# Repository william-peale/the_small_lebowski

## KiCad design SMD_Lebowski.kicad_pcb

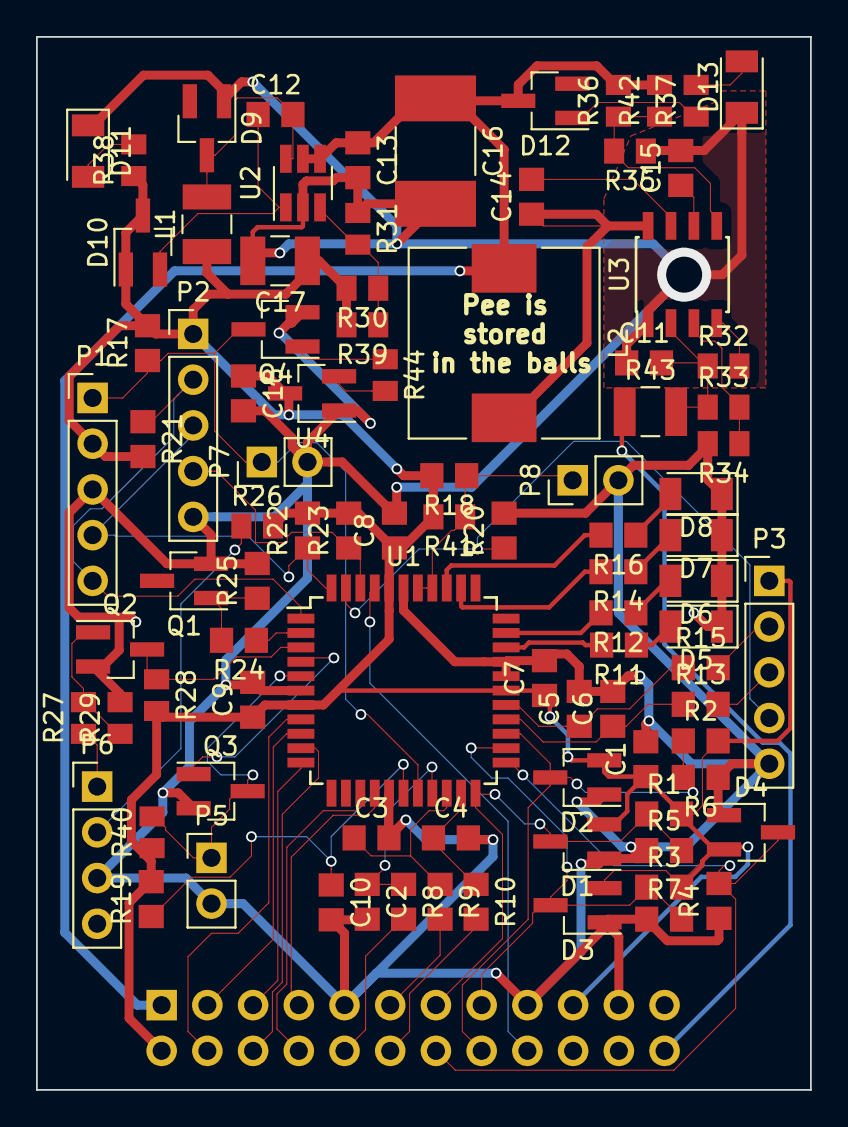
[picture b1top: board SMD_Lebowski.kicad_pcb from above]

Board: 2 copper layers, 43.0 x 58.5 mm, 93 parts (1 on the bottom side), 63 nets.

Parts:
C1, C5, C6, C7, C8, C9, C11, C13, C15, C18: 100n; C_0805_2012Metric_Pad1.29x1.40mm_HandSolder
C2, C3, C4, C12, C14: 10n; C_0805_2012Metric_Pad1.29x1.40mm_HandSolder
C10: 1u; C_0805_2012Metric_Pad1.29x1.40mm_HandSolder
C16: 33u; C_2816_7142Metric_Pad2.55x4.50mm_HandSolder
C17: 10u; C_1210_3225Metric_Pad1.39x2.70mm_HandSolder
D1, D2, D3, D4, D10: bat54s; SOT-23_Handsoldering
D5: red; LED_1206_3216Metric_Pad1.22x1.80mm_HandSolder
D6: orange; LED_1206_3216Metric_Pad1.22x1.80mm_HandSolder
D7: yellow; LED_1206_3216Metric_Pad1.22x1.80mm_HandSolder
D8, D11, D13: green; LED_1206_3216Metric_Pad1.22x1.80mm_HandSolder
D9, D12: bzx84c39; SOT-23_Handsoldering
L1: 47uH; L_1210_3225Metric_Pad1.39x2.70mm_HandSolder
L2: 220uH; L_10.4x10.4_H4.8
P1, P2, P3: Conn_01x05; PinHeader_1x05_P2.54mm_Vertical
P4: Conn_02x12_Odd_Even; PinHeader_2x12_P2.54mm_Vertical
P5, P7, P8: Conn_01x02; PinHeader_1x02_P2.54mm_Vertical
P6: Conn_01x03; PinHeader_1x04_P2.54mm_Vertical
Q1, Q2, Q3: BC807; SOT-23_Handsoldering
Q4: BC817; SOT-23_Handsoldering
R1, R2, R3, R4, R5, R6, R7: 22k; R_0805_2012Metric_Pad1.29x1.40mm_HandSolder
R8, R9, R10, R13, R15: 1k; R_0805_2012Metric_Pad1.29x1.40mm_HandSolder
R11, R12, R14, R16, R25: 680; R_0805_2012Metric_Pad1.29x1.40mm_HandSolder
R17, R18, R21, R22, R23: 4k7; R_0805_2012Metric_Pad1.29x1.40mm_HandSolder
R19: 10; R_0805_2012Metric_Pad1.29x1.40mm_HandSolder
R20, R24: 2k2; R_0805_2012Metric_Pad1.29x1.40mm_HandSolder
R26, R27, R28, R40, R41: 2k2; R_0805_2012Metric
R29, R37, R38: 680; R_0805_2012Metric
R30: 120k; R_0805_2012Metric
R31: 22k; R_0805_2012Metric
R32: 100k; R_0805_2012Metric
R33: 560k; R_0805_2012Metric
R34: 33k; R_0805_2012Metric
R35: 18k; R_0805_2012Metric
R36: 220k; R_0805_2012Metric
R39, R42: nf; R_0805_2012Metric
R43: 4.7; R_1210_3225Metric
R44: 4k7; R_0805_2012Metric
U1: PIC30F4011; TQFP-44_10x10mm_P0.8mm
U2: mpc16301; SOT-23-6_Handsoldering
U3: lm5017; SOIC-8_3.9x4.9mm_P1.27mm
U4: max809; SOT-23_Handsoldering

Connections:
+5V: C1.1, C7.1, C8.1, C9.1, C17.1, C18.1, D1.2, D2.2, D3.2, D4.2, D10.1, D10.3, L1.1, P1.2, P2.1, P3.1, P4.2, P4.19, R1.2, R2.2, R3.2, R17.2, R18.2, R19.2, R21.2, R22.2, R23.2, R26.2, R28.2, R30.2, R38.1, R39.2, R40.1, R41.2, U1.7, U1.28, U1.40, U4.3
+15V: C13.1, C16.1, D12.3, L2.1, P4.1, R36.2, R42.2, U2.4, U2.5
AFB: D1.3, P4.13, R1.1, R5.2, U1.22
BAT: D4.3, P4.14, R4.2, U1.23
BFB: D2.3, P4.16, R2.1, R6.2, U1.25
BPOW: P4.24, R43.1
CFB: D3.3, P4.15, R3.1, R7.2, U1.24
GLA: P4.7, U1.15
GLB: P4.5, U1.11
GLC: P4.3, U1.9
GND: C1.2, C2.2, C3.2, C4.2, C5.2, C6.2, C7.2, C8.2, C9.2, C10.2, C11.1, C13.2, C15.2, C16.2, C17.2, C18.2, D1.1, D2.1, D3.1, D4.1, D5.1, D6.1, D7.1, D8.1, D9.1, D11.1, D13.1, P1.3, P2.5, P3.5, P4.9, P4.17, P4.21, P5.2, P6.3, P7.2, P8.2, Q1.2, Q2.2, Q3.2, Q4.2, R4.1, R5.1, R6.1, R7.1, R20.2, R25.2, R29.2, R31.1, R34.2, R35.1, U1.6, U1.16, U1.29, U1.30, U1.39, U2.2, U3.1, U4.1
GUA: P4.8, U1.14
GUB: P4.6, U1.10
GUC: P4.4, U1.8
HALL1: P1.5, P2.2, R21.1, U1.1
HALL2: P1.4, P2.3, R22.1, U1.44
HALL3: P2.4, R23.1, U1.42
IA: P4.10, R8.2
IB: P4.11, R9.2
IC: P4.12, R10.2
NRES: P1.1, P7.1, Q4.3, R17.1, U1.18
unnamed: C2.1, R8.1, U1.19
unnamed: C3.1, R9.1, U1.20
unnamed: C4.1, R10.1, U1.21
unnamed: C5.1, R15.1, U1.27
unnamed: C6.1, R13.1, U1.26
unnamed: C10.1, R19.1, U1.17
unnamed: C11.2, R32.1, R33.1, R43.2, U3.2
unnamed: C12.1, D10.2, U2.1
unnamed: C12.2, D9.3, L1.2, U2.6
unnamed: C14.1, L2.2, U3.8
unnamed: C14.2, U3.7
unnamed: C15.1, U3.6
unnamed: D5.2, R11.1
unnamed: D6.2, R12.1
unnamed: D7.2, R14.1
unnamed: D8.2, R16.1
unnamed: D11.2, R38.2
unnamed: D12.1, R37.1
unnamed: D13.2, R37.2
unnamed: P6.1, R27.1
unnamed: P6.2, R26.1
unnamed: Q1.1, R24.2, R25.1
unnamed: Q2.1, R27.2, R29.1
unnamed: Q4.1, R44.1
unnamed: R11.2, U1.31
unnamed: R12.2, U1.32
unnamed: R14.2, U1.35
unnamed: R16.2, U1.36
unnamed: R30.1, R31.2, R39.1, U2.3
unnamed: R32.2, U3.4
unnamed: R33.2, R34.1, U3.3
unnamed: R35.2, R36.1, R42.1, U3.5
unnamed: R44.2, U4.2
R232: Q2.3, R28.1, U1.3
RCAN: P5.1, Q3.3, R40.2, U1.5
READY: P4.18, U1.41
REV: P3.4, R20.1, U1.43
SETUP: P8.1, R18.1, R41.1, U1.37, U1.38
T232: R24.1, U1.2
TCAN: Q3.1, U1.4
TH1: P3.3, R13.2
TH2: P3.2, R15.2

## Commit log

2018-06-21 bvmsss
2018-06-21 work 06/20
2018-06-23 finished sch
2018-06-23 finished sc
2018-06-24 Finished board layout
2018-06-24 finished
2018-06-30 routing n stuff
